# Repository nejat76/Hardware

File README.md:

# Hardware
My Hobby Electronic Projects

## Beware, none of these are actively developed at the moment.

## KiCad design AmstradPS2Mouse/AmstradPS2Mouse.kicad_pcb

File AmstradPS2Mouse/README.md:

# Amstrad PS2 Mouse Interface

This is just a reimplementation of the existing hardware design made by Bryce from CPC Wiki. 

https://www.cpcwiki.eu/index.php/User:Bryce

Original was a single sided board and this was my take to convert it to dual layer by Kicad. One of my first ever designs so there are lots of rooms for improvement.

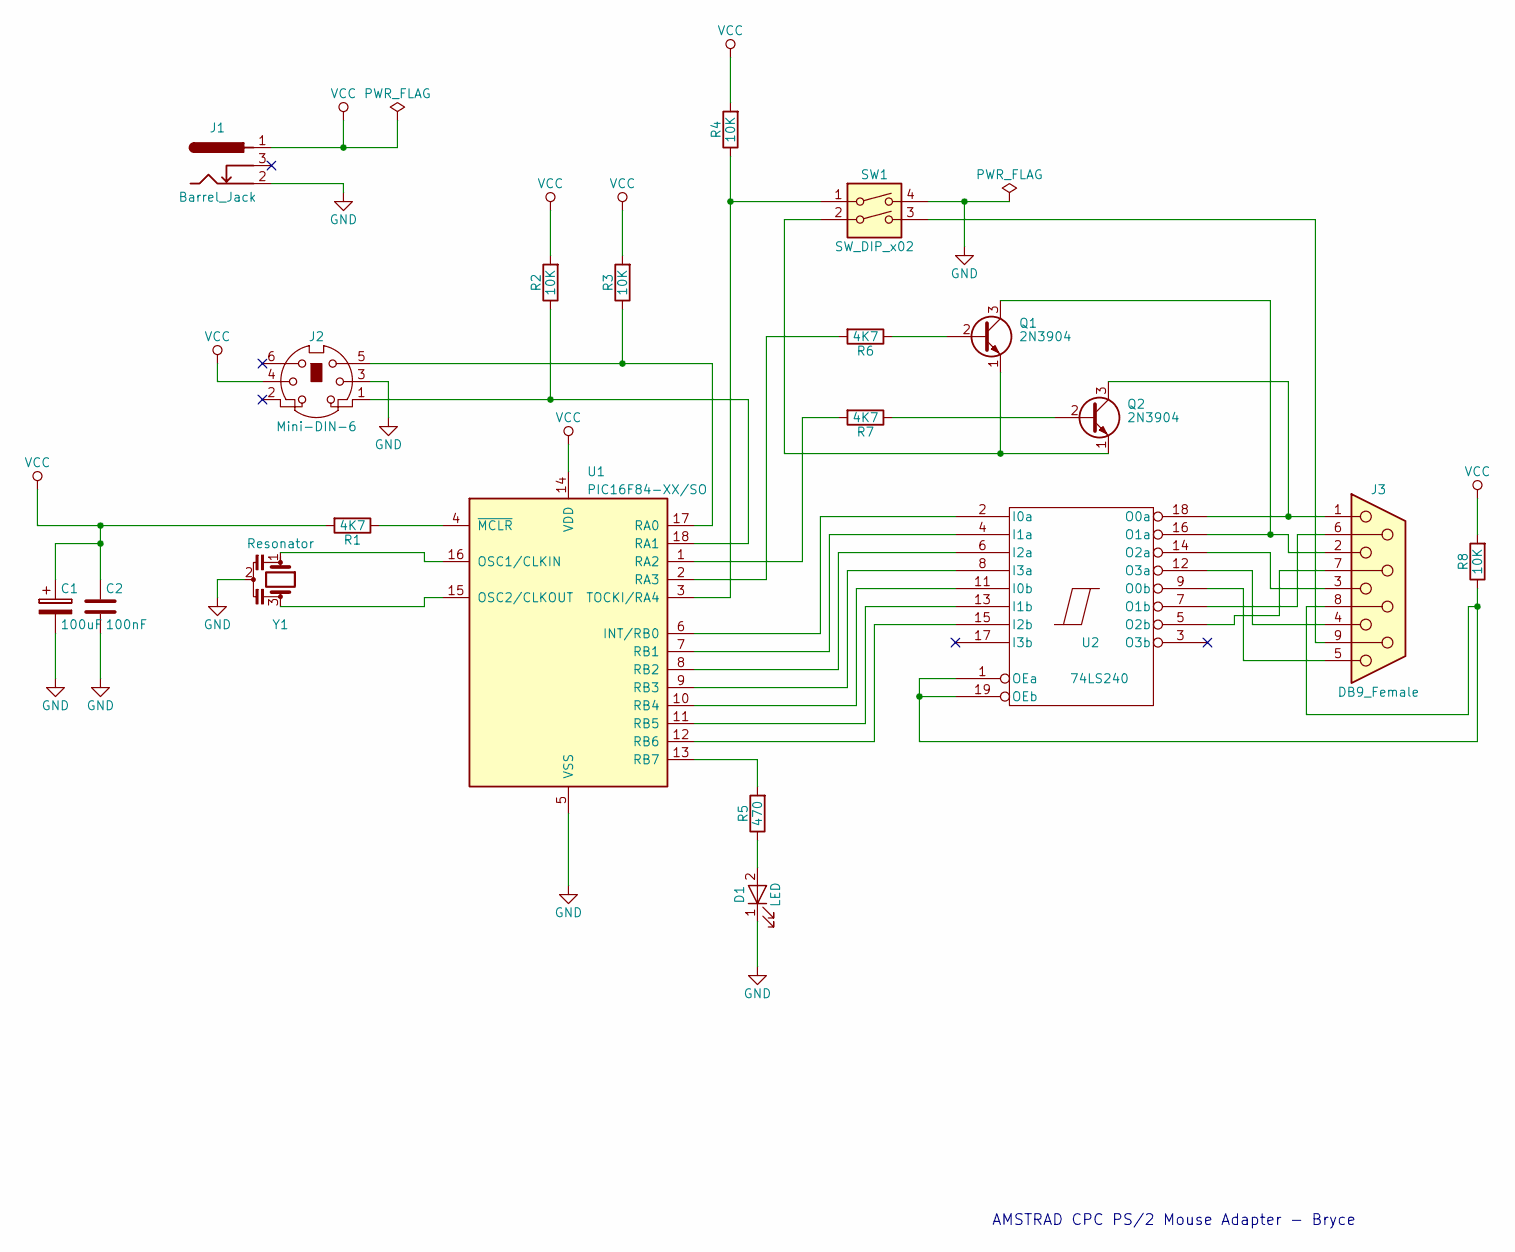
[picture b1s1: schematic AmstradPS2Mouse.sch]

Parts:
C1: 100uF; C_Disc_D11.0mm_W5.0mm_P5.00mm
C2: 100nF; C_Rect_L7.0mm_W3.5mm_P5.00mm
D1: LED; LED_D3.0mm_Horizontal_O1.27mm_Z2.0mm
J1: Barrel_Jack; BARREL_JACK
J2: Mini-DIN-6; din6-schurter-4850261
J3: DB9_Female; DSUB-9_Female_Horizontal_P2.77x2.84mm_EdgePinOffset7.70mm_H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
Q1, Q2: 2N3904; TO-92_Molded_Narrow
R1, R6, R7: 4K7; R_Axial_DIN0207_L6.3mm_D2.5mm_P7.62mm_Horizontal
R2, R3, R4, R8: 10K; R_Axial_DIN0207_L6.3mm_D2.5mm_P7.62mm_Horizontal
R5: 470; R_Axial_DIN0207_L6.3mm_D2.5mm_P7.62mm_Horizontal
SW1: SW_DIP_x02; SW_DIP_x2_W7.62mm_Slide
U1: PIC16F84-XX/SO; DIP-18_W7.62mm
U2: 74LS240; DIP-20_W7.62mm_Socket
Y1: Resonator; Resonator-3pin_w6.0mm_h3.0mm

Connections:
GND: C1.2, C2.2, D1.1 (K), J1.2, J2.3, SW1.4, U1.5 (VSS), U2.10 (GND), Y1.2
unnamed: D1.2 (A), R5.1
unnamed: J2.1, R2.1, U1.18 (RA1)
unnamed: J2.5, R3.1, U1.17 (RA0)
unnamed: J3.1, Q2.3 (C), U2.18 (O0a)
unnamed: J3.2, Q1.3 (C), U2.16 (O1a)
unnamed: J3.3, U2.14 (O2a)
unnamed: J3.4, U2.12 (O3a)
unnamed: J3.5, U2.9 (O0b)
unnamed: J3.6, U2.7 (O1b)
unnamed: J3.7, U2.5 (O2b)
unnamed: J3.8, R8.1, U2.1 (OEa), U2.19 (OEb)
unnamed: J3.9, SW1.3
unnamed: Q1.1 (E), Q2.1 (E), SW1.2
unnamed: Q1.2 (B), R6.1
unnamed: Q2.2 (B), R7.1
unnamed: R1.1, U1.4 (~MCLR~)
unnamed: R4.1, SW1.1, U1.3 (TOCKI/RA4)
unnamed: R5.2, U1.13 (RB7)
unnamed: R6.2, U1.2 (RA3)
unnamed: R7.2, U1.1 (RA2)
unnamed: U1.6 (INT/RB0), U2.2 (I0a)
unnamed: U1.7 (RB1), U2.4 (I1a)
unnamed: U1.8 (RB2), U2.6 (I2a)
unnamed: U1.9 (RB3), U2.8 (I3a)
unnamed: U1.10 (RB4), U2.11 (I0b)
unnamed: U1.11 (RB5), U2.13 (I1b)
unnamed: U1.12 (RB6), U2.15 (I2b)
unnamed: U1.15 (OSC2/CLKOUT), Y1.3
unnamed: U1.16 (OSC1/CLKIN), Y1.1
VCC: C1.1, C2.1, J1.1, J2.4, R1.2, R2.2, R3.2, R4.2, R8.2, U1.14 (VDD), U2.20 (VCC)

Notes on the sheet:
AMSTRAD CPC PS/2 Mouse Adapter - Bryce

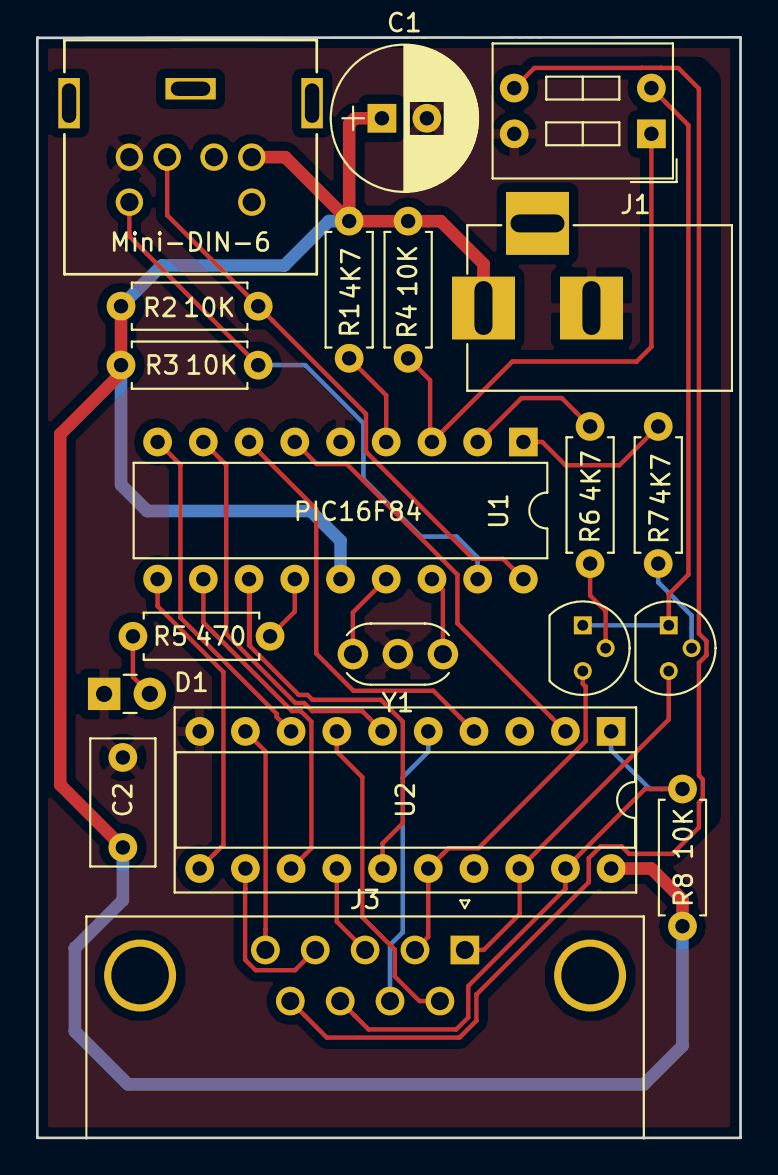
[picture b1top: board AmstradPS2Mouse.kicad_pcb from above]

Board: 2 copper layers, 39.1 x 61.1 mm, 20 parts (0 on the bottom side), 31 nets.

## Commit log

2023-03-21 Add Amstrad PS2 Mouse
2023-03-21 Add README
